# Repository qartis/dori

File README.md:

# DORI (Distributed Outdoor Robotic Instruments) is a remote-controlled robot project created by 3 university students at Simon Fraser University. More info here: http://dori.qartis.com/

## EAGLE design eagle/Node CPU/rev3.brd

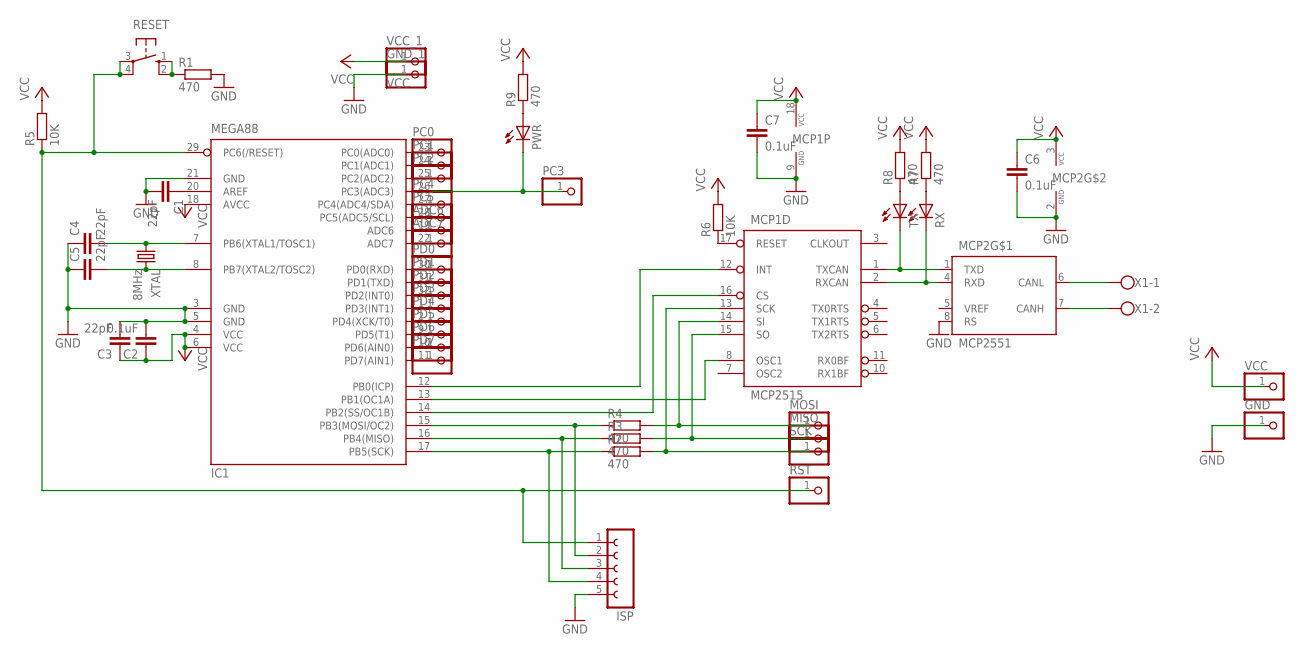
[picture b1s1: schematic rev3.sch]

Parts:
ADC6, ADC7: PINHD-1X1; 1X01
C1, C3, C4, C5: 22pF; C0603
C2, C6, C7: 0.1uF; C0603
GND: PINHD-1X1; 1X01
GND_1: PINHD-1X1; 1X01
IC1: MEGA88; TQFP32-08
ISP: FE05-1
MCP1: MCP2515; DIL18
MCP2: MCP2551; DIL08
MISO: PINHD-1X1; 1X01
MOSI: PINHD-1X1; 1X01
PC0, PC1, PC2, PC3, PC4, PC5: PINHD-1X1; 1X01
PD0, PD1, PD2, PD3, PD4, PD5, PD6, PD7: PINHD-1X1; 1X01
PWR: LEDCHIP-LED0603; CHIP-LED0603
R1, R2, R3, R4, R7, R8, R9: 470; R0603
R5, R6: 10K; R0603
RESET: 10-XX; B3F-10XX
RST: PINHD-1X1; 1X01
RX: LEDCHIP-LED0603; CHIP-LED0603
SCK: PINHD-1X1; 1X01
TX: LEDCHIP-LED0603; CHIP-LED0603
VCC: PINHD-1X1; 1X01
VCC_1: VCC; 1X01
X1: W237-102
XTAL: 8MHz; HC49/S

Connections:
GND: C1.2, C2.2, C3.2, C4.1, C5.1, C6.2, C7.2, GND.1, GND_1.1, IC1.3 (GND), IC1.5 (GND), IC1.21 (GND), ISP.5, MCP1.9 (GND), MCP2.2 (GND), MCP2.8 (RS), R1.2
unnamed: C1.1, IC1.20 (AREF)
unnamed: IC1.16 (PB4(MISO)), ISP.3, R3.1
unnamed: MCP1.14 (SI), MOSI.1, R4.2
unnamed: IC1.14 (PB2(SS/OC1B)), MCP1.16 (CS)
unnamed: IC1.13 (PB1(OC1A)), MCP1.8 (OSC1)
unnamed: MCP1.1 (TXCAN), MCP2.1 (TXD), TX.C
unnamed: C5.2, IC1.8 (PB7(XTAL2/TOSC2)), XTAL.2
unnamed: MCP2.6 (CANL), X1.1
unnamed: MCP1.17 (RESET), R6.1
unnamed: R1.1, RESET.1 (S), RESET.2 (S1)
unnamed: IC1.12 (PB0(ICP)), MCP1.12 (INT)
unnamed: MCP1.13 (SCK), R2.2, SCK.1
unnamed: MCP2.7 (CANH), X1.2
unnamed: IC1.15 (PB3(MOSI/OC2)), ISP.2, R4.1
unnamed: R8.1, TX.A
unnamed: R7.1, RX.A
unnamed: IC1.23 (PC0(ADC0)), PC0.1
unnamed: IC1.24 (PC1(ADC1)), PC1.1
unnamed: IC1.25 (PC2(ADC2)), PC2.1
unnamed: IC1.27 (PC4(ADC4/SDA)), PC4.1
unnamed: IC1.28 (PC5(ADC5/SCL)), PC5.1
unnamed: ADC6.1, IC1.19 (ADC6)
unnamed: ADC7.1, IC1.22 (ADC7)
unnamed: IC1.30 (PD0(RXD)), PD0.1
unnamed: IC1.31 (PD1(TXD)), PD1.1
unnamed: IC1.32 (PD2(INT0)), PD2.1
unnamed: IC1.1 (PD3(INT1)), PD3.1
unnamed: IC1.2 (PD4(XCK/T0)), PD4.1
unnamed: IC1.9 (PD5(T1)), PD5.1
unnamed: IC1.10 (PD6(AIN0)), PD6.1
unnamed: IC1.11 (PD7(AIN1)), PD7.1
unnamed: PWR.A, R9.1
unnamed: C4.2, IC1.7 (PB6(XTAL1/TOSC1)), XTAL.1
unnamed: MCP1.15 (SO), MISO.1, R3.2
unnamed: IC1.17 (PB5(SCK)), ISP.4, R2.1
unnamed: IC1.26 (PC3(ADC3)), PC3.1, PWR.C
RESET: IC1.29 (PC6(/RESET)), ISP.1, R5.1, RESET.3, RESET.4 (P1), RST.1
RXLED: MCP1.2 (RXCAN), MCP2.4 (RXD), RX.C
VCC: C2.1, C3.1, C6.1, C7.1, IC1.4 (VCC), IC1.6 (VCC), IC1.18 (AVCC), MCP1.18 (VCC), MCP2.3 (VCC), R5.2, R6.2, R7.2, R8.2, R9.2, VCC.1, VCC_1.1

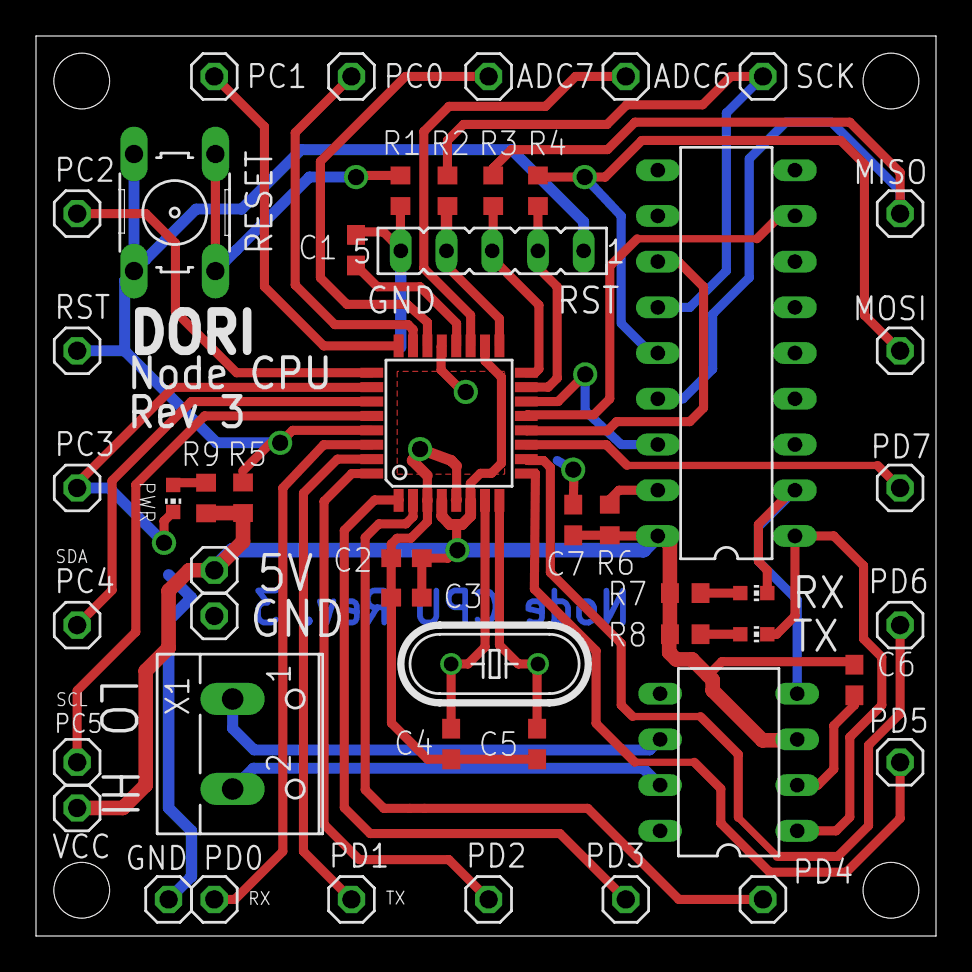
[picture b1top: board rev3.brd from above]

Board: 4 copper layers, 50.0 x 50.0 mm, 50 parts (0 on the bottom side), 40 nets.

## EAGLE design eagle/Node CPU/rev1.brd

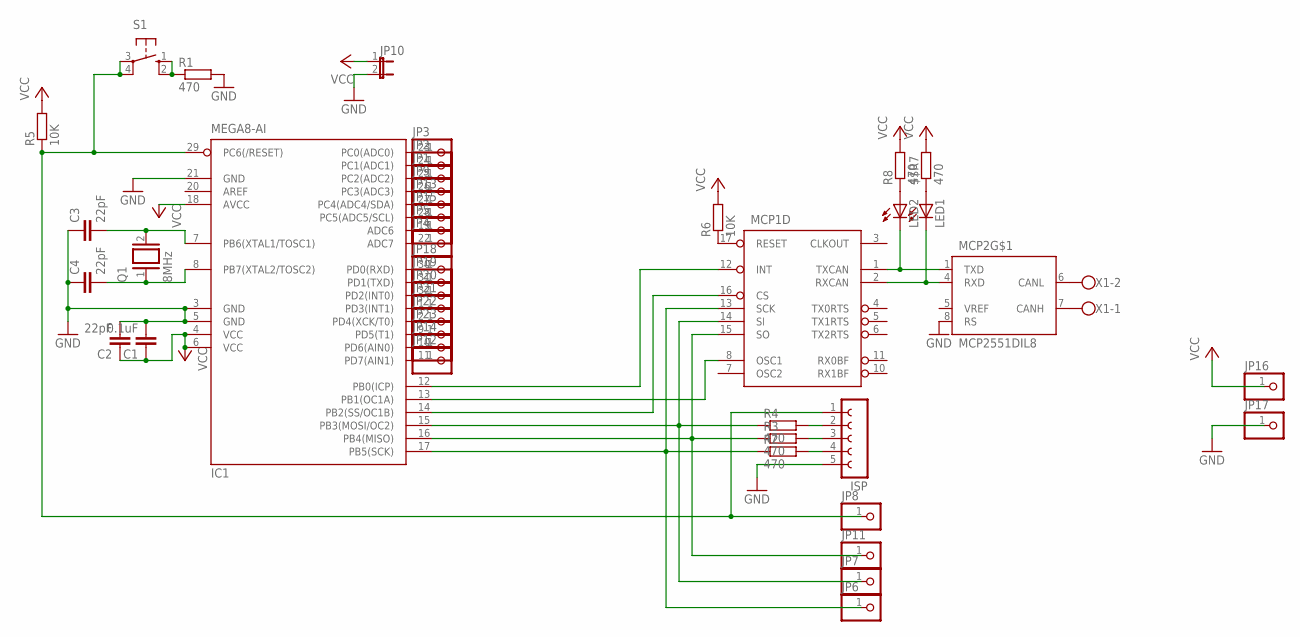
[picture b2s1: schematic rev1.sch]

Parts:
$$R7: 470; R0603
C1: 0.1uF; C0603
C2, C3, C4: 22pF; C0603
IC1: MEGA8-AI; TQFP32-08
ISP: FE05-1
JP1, JP2, JP3, JP4, JP5, JP6, JP7, JP8, JP9, JP11, JP12, JP13, JP14, JP15, JP16, JP17, JP18, JP19, JP20, JP21, JP22, JP23: PINHD-1X1; 1X01
JP10: JUMPER-2PTH; 1X02
LED1, LED2: LEDCHIP-LED0603; CHIP-LED0603
MCP1: MCP2515P; DIL18
MCP2: MCP2551DIL8; DIL08
Q1: 8MHz; QS
R1, R2, R3, R4, R8: 470; R0603
R5, R6: 10K; R0603
S1: 10-XX; B3F-10XX
X1: W237-102

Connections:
GND: C1.2, C2.2, C3.1, C4.1, IC1.3 (GND), IC1.5 (GND), IC1.21 (GND), ISP.5, JP10.2, JP17.1, MCP1.9 (GND), MCP2.2 (GND), MCP2.8 (RS), R1.2
unnamed: IC1.17 (PB5(SCK)), JP6.1, MCP1.13 (SCK), R2.1
unnamed: IC1.16 (PB4(MISO)), JP11.1, MCP1.15 (SO), R3.1
unnamed: IC1.15 (PB3(MOSI/OC2)), JP7.1, MCP1.14 (SI), R4.1
unnamed: IC1.14 (PB2(SS/OC1B)), MCP1.16 (CS)
unnamed: IC1.13 (PB1(OC1A)), MCP1.8 (OSC1)
unnamed: LED2.C, MCP1.1 (TXCAN), MCP2.1 (TXD)
unnamed: C4.2, IC1.8 (PB7(XTAL2/TOSC2)), Q1.1
unnamed: C3.2, IC1.7 (PB6(XTAL1/TOSC1)), Q1.2
unnamed: MCP1.17 (RESET), R6.1
unnamed: R1.1, S1.1 (S), S1.2 (S1)
unnamed: IC1.12 (PB0(ICP)), MCP1.12 (INT)
unnamed: ISP.2, R4.2
unnamed: ISP.3, R3.2
unnamed: ISP.4, R2.2
unnamed: LED2.A, R8.1
unnamed: $$R7.1, LED1.A
unnamed: IC1.23 (PC0(ADC0)), JP3.1
unnamed: IC1.24 (PC1(ADC1)), JP2.1
unnamed: IC1.25 (PC2(ADC2)), JP1.1
unnamed: IC1.26 (PC3(ADC3)), JP9.1
unnamed: IC1.27 (PC4(ADC4/SDA)), JP13.1
unnamed: IC1.28 (PC5(ADC5/SCL)), JP15.1
unnamed: IC1.19 (ADC6), JP5.1
unnamed: IC1.22 (ADC7), JP4.1
unnamed: IC1.30 (PD0(RXD)), JP18.1
unnamed: IC1.31 (PD1(TXD)), JP19.1
unnamed: IC1.32 (PD2(INT0)), JP20.1
unnamed: IC1.1 (PD3(INT1)), JP21.1
unnamed: IC1.2 (PD4(XCK/T0)), JP22.1
unnamed: IC1.9 (PD5(T1)), JP23.1
unnamed: IC1.10 (PD6(AIN0)), JP14.1
unnamed: IC1.11 (PD7(AIN1)), JP12.1
unnamed: MCP2.6 (CANL), X1.2
unnamed: MCP2.7 (CANH), X1.1
RESET: IC1.29 (PC6(/RESET)), ISP.1, JP8.1, R5.1, S1.3, S1.4 (P1)
RXLED: LED1.C, MCP1.2 (RXCAN), MCP2.4 (RXD)
VCC: $$R7.2, C1.1, C2.1, IC1.4 (VCC), IC1.6 (VCC), IC1.18 (AVCC), JP10.1, JP16.1, MCP1.18 (VCC), MCP2.3 (VCC), R5.2, R6.2, R8.2

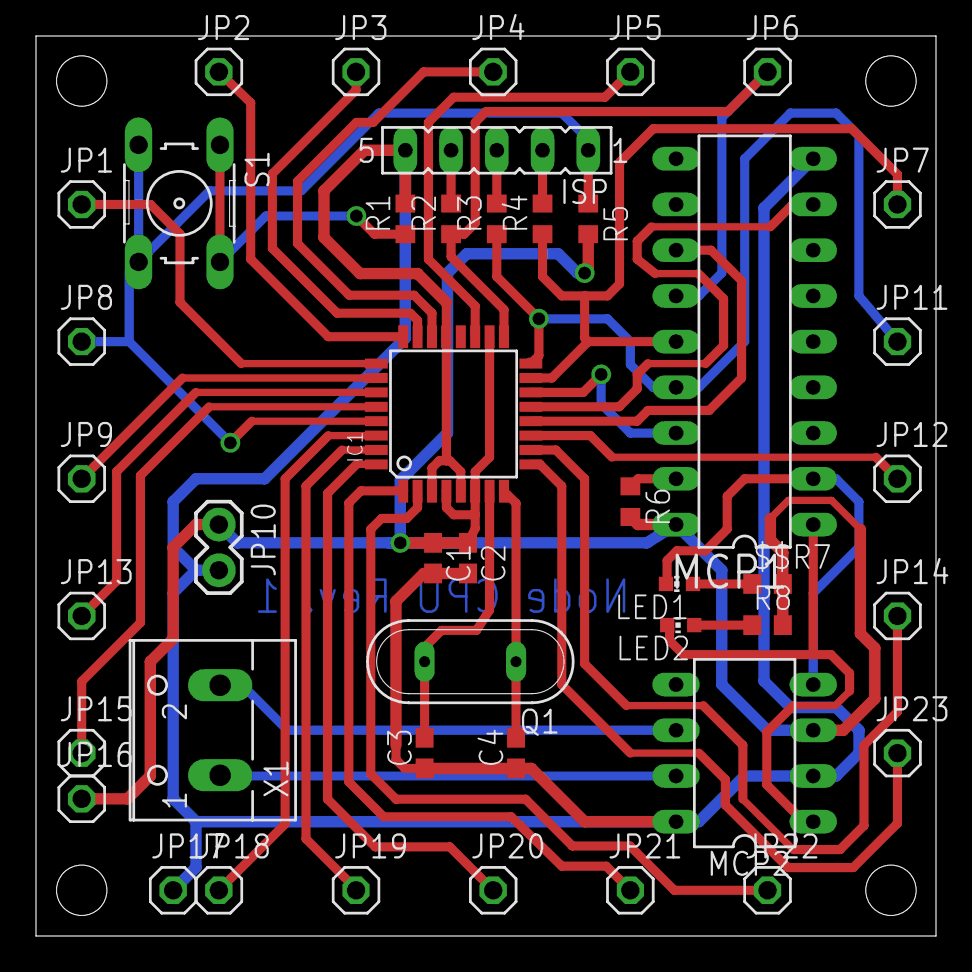
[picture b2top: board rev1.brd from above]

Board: 2 copper layers, 50.0 x 50.0 mm, 44 parts (0 on the bottom side), 38 nets.

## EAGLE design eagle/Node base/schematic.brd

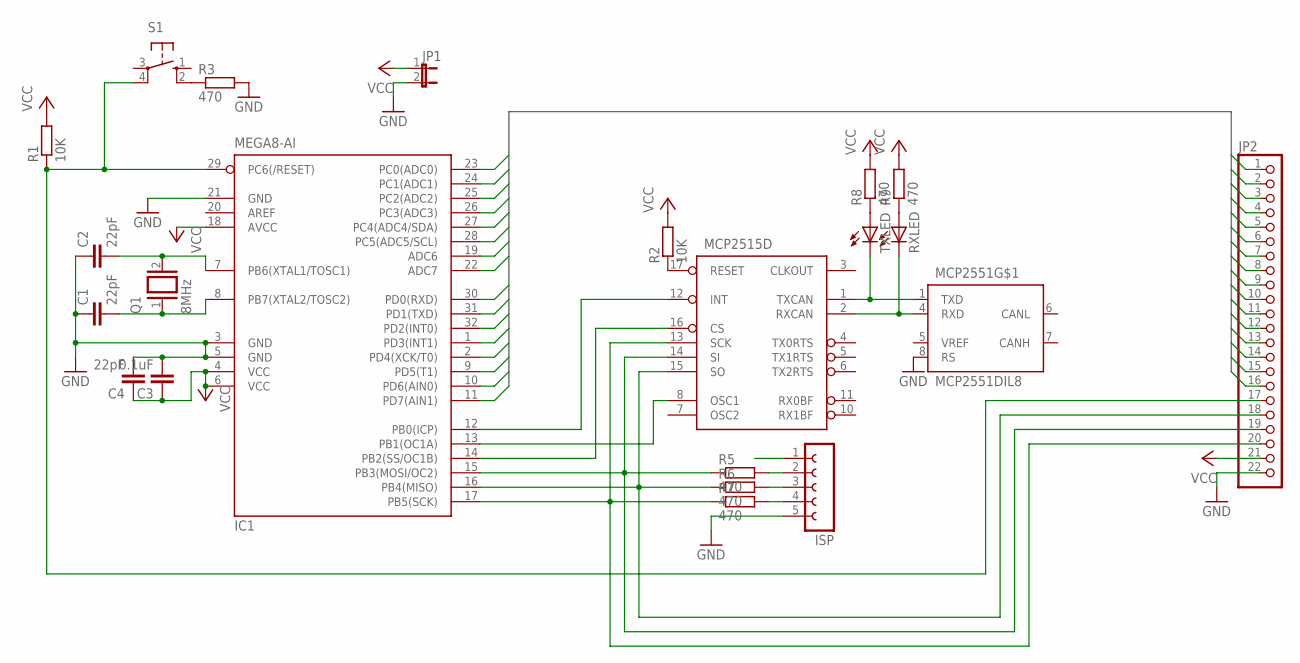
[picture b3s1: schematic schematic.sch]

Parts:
C1, C2, C4: 22pF; C0603
C3: 0.1uF; C0603
IC1: MEGA8-AI; TQFP32-08
ISP: FE05-1
JP1: JUMPER-2PTH; 1X02
JP2: PINHD-1X22/90; 1X22/90
MCP2515: MCP2515P; DIL18
MCP2551: MCP2551DIL8; DIL08
Q1: 8MHz; QS
R1, R2: 10K; R0603
R3, R5, R6, R7, R8, R9: 470; R0603
RXLED: LED; SMARTLED-TTW
S1: 10-XX; B3F-10XX
TXLED: LED; SMARTLED-TTW

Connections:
GND: C1.1, C2.1, C3.2, C4.2, IC1.3 (GND), IC1.5 (GND), IC1.21 (GND), ISP.5, JP1.2, JP2.22, MCP2515.9 (GND), MCP2551.2 (GND), MCP2551.8 (RS), R3.2
unnamed: IC1.17 (PB5(SCK)), JP2.20, MCP2515.13 (SCK), R7.1
unnamed: IC1.16 (PB4(MISO)), JP2.18, MCP2515.15 (SO), R6.1
unnamed: IC1.15 (PB3(MOSI/OC2)), JP2.19, MCP2515.14 (SI), R5.1
unnamed: IC1.14 (PB2(SS/OC1B)), MCP2515.16 (CS)
unnamed: IC1.13 (PB1(OC1A)), MCP2515.8 (OSC1)
unnamed: MCP2515.1 (TXCAN), MCP2551.1 (TXD), TXLED.C@1 (C)
unnamed: C1.2, IC1.8 (PB7(XTAL2/TOSC2)), Q1.1
unnamed: C2.2, IC1.7 (PB6(XTAL1/TOSC1)), Q1.2
unnamed: MCP2515.17 (RESET), R2.1
unnamed: R3.1, S1.2 (S1)
unnamed: IC1.12 (PB0(ICP)), MCP2515.12 (INT)
unnamed: ISP.2, R5.2
unnamed: ISP.3, R6.2
unnamed: ISP.4, R7.2
unnamed: R8.1, TXLED.A@1 (A)
unnamed: R9.1, RXLED.A@1 (A)
PC0: IC1.23 (PC0(ADC0)), JP2.1
PC1: IC1.24 (PC1(ADC1)), JP2.2
PC2: IC1.25 (PC2(ADC2)), JP2.3
PC3: IC1.26 (PC3(ADC3)), JP2.4
PC4: IC1.27 (PC4(ADC4/SDA)), JP2.5
PC5: IC1.28 (PC5(ADC5/SCL)), JP2.6
PC6: IC1.19 (ADC6), JP2.7
PC7: IC1.22 (ADC7), JP2.8
PD0: IC1.30 (PD0(RXD)), JP2.9
PD1: IC1.31 (PD1(TXD)), JP2.10
PD2: IC1.32 (PD2(INT0)), JP2.11
PD3: IC1.1 (PD3(INT1)), JP2.12
PD4: IC1.2 (PD4(XCK/T0)), JP2.13
PD5: IC1.9 (PD5(T1)), JP2.14
PD6: IC1.10 (PD6(AIN0)), JP2.15
PD7: IC1.11 (PD7(AIN1)), JP2.16
RESET: IC1.29 (PC6(/RESET)), ISP.1, JP2.17, R1.1, S1.4 (P1)
RXLED: MCP2515.2 (RXCAN), MCP2551.4 (RXD), RXLED.C@1 (C)
VCC: C3.1, C4.1, IC1.4 (VCC), IC1.6 (VCC), IC1.18 (AVCC), JP1.1, JP2.21, MCP2515.18 (VCC), MCP2551.3 (VCC), R1.2, R2.2, R8.2, R9.2

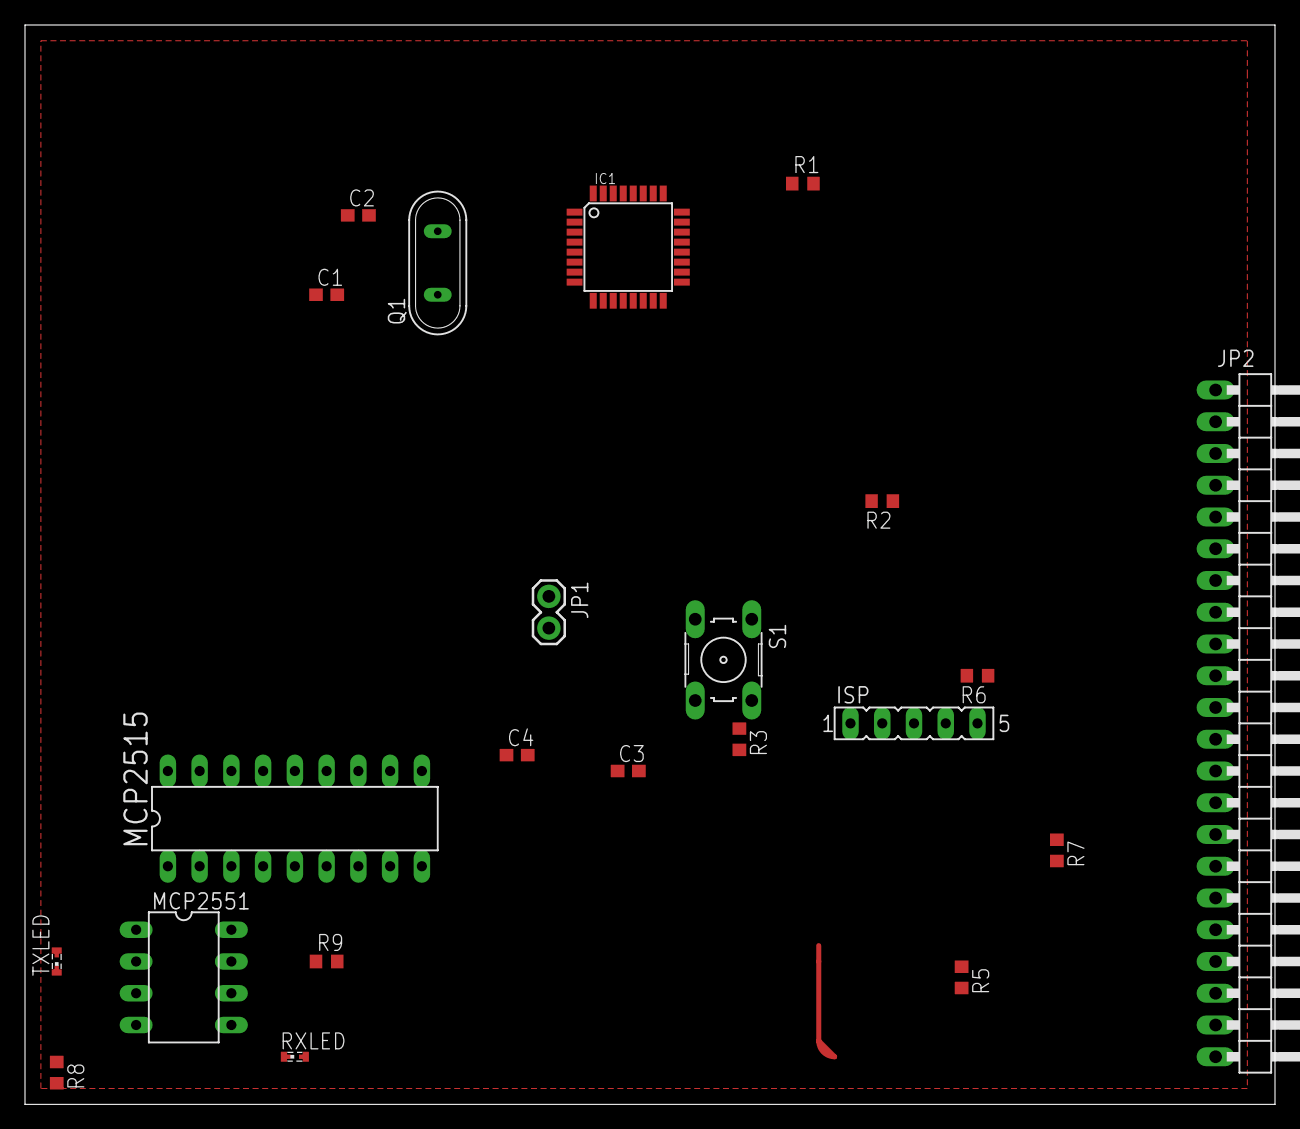
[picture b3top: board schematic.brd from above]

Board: 2 copper layers, 100.0 x 86.3 mm, 22 parts (0 on the bottom side), 36 nets.

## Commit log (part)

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2013-08-03 sd basic file transfer works
2013-08-03 modem can pass CAN traffic back and forth now through TCP
2013-08-03 sniffer's id is now ID_ANY
2013-08-03 9dof now accepts uart debug commands as well as nmea
2013-08-03 parse_nmea(char *) now returns uint8_t
2013-08-03 add debug_flush to fix out-of-sync issue when hitting enter during ISR
2013-08-03 add get_mcusr in .init3 to fix watchdog reboot cycle, print reboot source
2013-08-03 IRQ_TIMER renamed to IRQ_PERIODIC
2013-08-03 change uart buf size to 32
2013-08-03 move can.h to /
2013-08-03 add decan.c tool to decode raw can frames to ascii
2013-08-03 First attempt at shell->gateway->dori file transfer
2013-08-05 Updated can types and made shared can name code
2013-08-06 add dcim_read and dcim_header CAN messages
2013-08-06 rename at_n_read -> at_n_write
2013-08-06 remove unnecessary casts
2013-08-08 add TYPE_dcim_len
2013-08-08 file tree is now recursive
2013-08-09 Updated gateway and send file transfer code to close files on new transfer headers. Added 'D' flag for send so that you can send on port 53 instead of 1338 (to pretend to be DORI)
2013-08-11 Updated gitignore to include siteobjects.db
2013-08-11 Built the toolbar into the SiteEditor. Fixed a couple mouse dragging and colour changing bugs. Cleaned up SiteEditor::handle()
2013-08-20 First iteration of the integrated sidebar with Fl_Tree of SiteObjects. Supports listing of all SiteObjects, ordered by site or type. Still need to make the tree objects cause the SiteObject to be sel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
2013-09-08 add ut390 driver
2013-10-06 UT390 basic functionality controlled over UART
2013-10-06 Added 5.5V support using ADC for UT390 V+ output
2013-10-11 Laser has CAN driver, started adding tag system
2013-10-19 nodes have custom hardware bases now
2013-10-19 remove windows line endings..
2013-10-19 Updated arm and stepper CAN driver
2013-10-24 Cleaned up prints and enabled laser measurement on CAN request
2013-10-25 add enviro module
2013-10-25 Added basic CAN functionality to enviro
2013-10-27 9dof fully CANifyied and enviro cleaned up
2013-10-27 Implemented nostfu and stfu
2013-11-07 Added backspace support to uart. Mostly fixed timing issue in logger
2013-11-08 Fixed file_tree timing issue by wrapping sd card calls in atomic blocks
2013-11-08 Updated mcp2515_xfer to take sensor id
2013-11-14 Added initial modemb code
2013-11-14 Initial fbus + user_irq code
2013-11-20 add SMS receive support, add fbus heartbeat support, add fbus subscribe support
2013-11-20 uart now uses interrupt-based tx buffer
2013-11-20 nodes with custom uart irq don't check IRQ_UART signal
2013-11-20 simple SMS sending
2013-11-23 re-named and organized sms frame statuses
2013-11-23 CAN packet logging and notifying
2013-11-23 move adc code into adc.{c,h}
2013-11-23 fix line endings in time.c
2013-11-23 add adc.o and temp.o to diag/Makefile
2013-11-23 temp.{c,h} moved to avr/
2013-11-23 move temperature driver to avr/ to be shared by enviro/ and diag/
2013-11-23 add adc.o and temp.o to enviro/Makefile
2013-11-23 move adc code out of arm/
2013-11-23 add ONLCR to avr/drive
2013-11-23 change baudconv's hardware buffers to 512 bytes
2013-11-23 update doc/nodelist as of nov 2013
2013-11-23 can_names are now const
2013-11-23 cleanup printfs in compass_test
2013-11-24 fix timer: 1 second timer was ticking every (250/248) seconds
2013-11-24 avr/diag now uses 328p
2013-11-25 phone debug interrupt based
2013-11-25 diag: send voltage in can_irq
2013-12-31 add printwait_P
2013-12-31 mcp2515: add mcp2515_dump to view registers
2013-12-31 clean up whitespace
2013-12-31 diag: add power reduction headers
2013-12-31 logger: remove sram.o from build
2013-12-31 add cscope to .gitignore
2013-12-31 add power reduction #includes to remaining nodes
2014-01-11 Basic ircam driver. Sends camera data over CAN 8 bytes at a time
2014-01-12 Converted image capture to use CAN + CTS
2014-01-15 modemb automatically deletes SMSs after processing them
2014-01-24 Added simple error handling and auto subscribing on chip bootup and some debug statements when sending CAN packages as SMS
2014-01-28 Added missing power includes to ut390
2014-02-02 update Makefiles for enviro and ut390
2014-02-09 Updated modema code to partially working state (parsing TCPIP received data still buggy). Updated laser. Updated gateway. Updated shell/send
2014-02-09 Added ircam makefile
2014-02-13 Removed concept of 'active' nodes. Cleaned up
2014-02-15 Updated ircam to use xfer_chunk type
2014-02-15 Updated modema to handle sensor data
2014-02-15 add ut390 laser code to arm node
2014-02-15 move internal ut390 laser definitions to separate header
2014-02-15 add laser connections to arm/pinout.txt
2014-02-15 Updated logger and send to be sensor-aware
2014-02-15 Fixed gateway fd bug
2014-02-18 Initial merge of ircam and logger. #define'd out dcim and fat code
2014-02-18 Moved ircam code to old/
2014-02-18 mcp: messages now timeout on MERR
2014-02-18 Added buffered transmissions of 512 bytes
2014-02-18 Added gateway safety checks
2014-02-18 Added invalid sentinels CAN IDs and SENSOR lists
2014-02-18 512 byte net_send_buf attempt
2014-02-20 modema: add pinout.txt
2014-02-20 temp: rename num_sensors -> temp_num_sensors
2014-02-20 1wire: bus moved to PC2
2014-02-20 debug: putchar is now atomic
2014-02-20 time: add timer_tophalf function in interrupt context
2014-02-21 Arm now responds to CAN. Temporarily disabled arm control because relays are sharing debug pins
2014-02-21 Timeout no longer kills gateway
2014-02-21 Updated timing logic for periodics
2014-02-21 Changed to 8MHZ
2014-02-21 Add modema powercycle over CAN
2014-02-22 add 1.8432MHz xtal settings to timer0
2014-02-22 Added ircam files to logger
2014-02-22 fbus.c: get rid of unused variables
2014-02-22 modema uses 18.432MHz clock
2014-02-22 modema: change some timings during tcp connection
2014-02-22 9dof: nmea parser uses PROGMEM strings
2014-02-23 uart: uart_getchar is hidden if UART_CUSTOM_INTERRUPT
2014-02-23 arm position can be controlled over debug
2014-02-23 diag: heating pads automatically controlled via TIMER_TOPHALF and USER_IRQ
2014-02-23 diag: update pinout.txt with 1wire connections
2014-02-23 drive: enable uart echo
2014-02-23 drive: main returns int
2014-02-23 enviro: add uart_irq handler for debugging
2014-02-23 node.h: only check irq return status if it's valid
2014-02-23 mcp2515: SENSOR_time updates can be any packet type
2014-02-23 logger: now uses 88p
2014-02-23 ut390: add error handling
2014-02-23 Make time update only for explicit and periodic
2014-02-23 9dof: re-add debug_irq and debug.o
2014-02-23 9dof: fix integer promotion error in time broadcasts
2014-02-23 mcp: retry 3 times if mcp2515_xfer misses a CTS
2014-02-23 logger: now uses 328p
2014-02-23 logger: implicitly handle xfer cancels
2014-02-23 move powershot to avr/old/
2014-02-23 add some pretty printing to decan
2014-02-23 add baudconv/Makefile
2014-02-23 diag: remove duplicated code between can_irq and periodic_irq
2014-02-23 node.h: don't turn off i2c and timer2 (debug) on sleep
2014-02-23 time.c: make heartbeat light blink quicker
2014-02-23 update todo with pre-launch tasks, and remove old GUI tasks
2014-02-23 mcp: remove final printfs
2014-02-25 mcp: argument order now follows struct member order (type, id, sensor, data, len)
2014-02-25 modema: send sensor error when we timeout during EXPECTING_PROMPT
2014-02-26 decan: add pretty printing for SENSOR_{current,temp,time}
2014-02-26 gateway: send sensor as big-endian
2014-02-26 Added pretty printing for laser measure distances in decan
2014-02-26 decan: remove extra newline
2014-03-02 Added updated powercycling and tcp buffering
2014-03-02 decan: add colored output
2014-03-04 temp.c: reduce debug message lengths
2014-03-04 modema: go into STATE_ERROR if we don't see a sim900 prompt
2014-03-04 modema: add action_modema_connect and action_modema_disconnect handling
2014-03-06 Removed static variables from ircam fbuf reading
2014-03-12 laser: use the `nDist` line from the output, because it matches the screen
2014-03-12 laser: lowpass filter adc line to avoid noise
2014-03-12 laser: force laser off after rapidfire mode
2014-03-12 laser: send line_num as CAN sensor error payload
2014-03-12 mcp2515: remove last debug messages
2014-03-12 diag: current sensor now has op-amp, so mA calculation has changed
2014-03-12 enviro: now uses 328p
2014-03-16 arm: speed up laser measurements
2014-03-16 arm: stepper now remembers its state, can accept absolute positioning actions
2014-03-19 arm: add synchronized laser_sweep routine between laser and stepper
2014-03-20 mcp2515: fix xfer cancel bug. update arm and cam to use new mcp2515_xfer_begin() interface
2014-03-20 modemb: code cleanups
2014-03-23 modemb: add TYPE_set_sms_dest command
2014-03-24 decan: use SI units
2014-03-24 Simplified write_to_client()
2014-03-25 laser: give up sweep after 10 errors total
2014-03-25 laser: return 0mm from `measure` to force stepper to move past any nonreflective spots
2014-03-25 laser: update pinout.txt
2014-03-25 add uptime and TYPE_value_request SENSOR_uptime command
2014-03-27 Added return value checking for DORI's writes to shell
2014-03-27 gateway: add handler for laser sweeps
2014-03-28 Always request fbus ID before sending SMS
2014-03-29 arm: use stepper_set_stepsize in stepper_init
2014-03-29 arm: arm motion is judged to succeed based on timeout status, not final position
2014-03-29 modema: send nops every 30s
2014-03-29 Added sensor testing script
2014-03-29 Fixed error in sensor tests script
2014-03-29 Moved decan to shell
2014-03-30 9dof: value_request coords returns an error if no valid data available
2014-03-30 saleae_plugin: add `sensor` field from extended id
2014-03-30 9dof: don't bail on error during send_all_can
2014-03-30 arm: handle uptime requests
2014-03-30 arm: laser_sweep_begin now accepts start_angle, end_angle, stepsize args
2014-03-30 gateway: initialize empty data_str if no data bytes will be copied
2014-04-02 can.h: add TYPE_drive_done
2014-04-02 mcp2515: remove unneeded sd.h
2014-04-05 Using a 32 bit unsigned integer to store rain count
2014-04-05 Fixed arm doing a sweep passed the specified end position
2014-04-05 modemb: add sos_nopsled command
2014-04-05 Added error codes for ircam error cases
2014-04-06 Added drive and cam uptime requests to sensor testing script
2014-04-10 tk: get rid of live updating
2014-04-12 mcp: reinit chip on receive buf 0 overflow
2014-04-12 mcp: add intf to mcp2515_dump
2014-04-13 node.h: delay 5s on bootup to allow power to settle
2014-04-13 enviro: low-pass filter the wind adc before output
2014-04-13 modema: catch the CIPSEND prompt in a more reliable way
2014-04-13 arm: laser will always be turned off after a sweep, and precision increased 10x
2014-04-13 sniffer: enter blank uart line to repeat previous command
2014-04-13 node.h: change 5s delay to 1s on bootup
2014-04-16 shell: add delaser and plotlaser tools
2014-04-17 Calibrated arm angles to linear degrees
2014-04-17 arm: fix laser infinite loop after sweep finishes
2014-04-18 mcp: reinit on error
2014-04-22 shell: use rm -f in make clean to avoid warnings
2014-04-22 modema: add '?' and 'm' commands to dump mcp status
2014-04-22 tests: add uptime_tests.sh
2014-04-24 start big irq cleanup
2014-04-30 Gateway: Increased max # of clients
2014-04-30 Gateway: Writes are non-blocking
2014-05-21 can.h: add SENSOR_{boot,interval,ircam}
2014-05-21 time.c: don't reset watchdog unless we've heard CAN traffic recently
2014-05-21 debug: disable debug timer when not in use
2014-05-21 avr: all nodes use new can_irq event loop
2014-05-21 decan: show uptime even if it's 0
2014-05-21 mcp: fix xfer bug, xfer resends now get sensor <- SENSOR_invalid
2014-05-21 modema: use can_ring buffer
2014-05-21 modemb: remove old "timer.h" include
2014-05-21 decan: pretty-printing of SENSOR_{boot,interval}
2014-05-21 shell: uptime_tests now delays 1s between requests
2014-05-23 Temp commit while debugging
2014-06-04 add missing ring.h
2014-06-19 spi: Wrapped spi write in atomic block
2014-07-05 node: replaced uart_tx_flush with delay
2014-07-09 Added node_debug_common
2014-07-11 diag: delay much shorter time when taking a current measurement (10s -> 0.5s)
2014-07-25 diag: don't send nonexistant temp values

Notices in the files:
parts and their libraries:
SparkFun-Passives: Licensing: CC v3.0 Share-Alike You are welcome to use this library for commercial purposes.
